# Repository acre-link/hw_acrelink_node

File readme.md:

# AcreLink Node

- Designed for a sleep current around 6 to 7 uA. 
- ESP32
- RFM95 Lora Module
- 868MHz PCB antenna, can be cut off and replaced by an SMA connector
- AA size lithium battery driven: (LS14500 Lithium-Thionyl-Chlorid or LifePo4 possible)
- Boost converter to supply sensors with stable 5V. Can be switched off for low current sleep mode
- External connector for Onewire, analog inputs and I2C including ESD protection with very low current TVS diodes
- Sensing battery voltage. Can be disabled for low sleep current
- Red led for signaling activity
- SPI header for external connection. 
- Mechanical switch to select battery of external power supply 
- Separate removable pcb section with wide range power supply 5 - 25V,  USB-C connector and USB-UART adapter for programming
- Enableable current measurement at GND level with 1 Ohm Resistor and low pass filtering. 
- Switchable Onewire power, data and datapullup, I2C power and pull ups. 

## 3D Preview 

## Pin Mapping ESP32
- AnalogInput1 : PIN13  GPIO14  ADC2_CH6
- Analog Bat   : PIN16  GPIO13  ADC2_CH4 
- AnalogInput2 : PIN11 GPIO26   ADC2_CH9
- I2C SDA	   : PIN33 GPIO21 		
- I2C SCL 	   : PIN36  GPIO22     
- UART2_RX     : PIN27 GPIO16        
- UART2_TX     : PIN28 GPIO17 		 
- 5V Buck EN   : PIN12 GPIO27 		
- LED_Signal   : PIN9 GPIO33
- RFM_MISO     : PIN31  GPIO19 
- RFM_MOSI     : PIN37  GPIO23 
- RFM_SCK      : PIN30  GPIO18
- RFM_CS       : PIN29  GPIO5
- RFM_RST      : PIN23  GPIO15 
- RFM_IRQ/DIO0 : PIN26  GPIO4 
- RFM_DIO1     : PIN8   GPIO32 	

## Links
- Antenna Design: https://github.com/cernohorsky/LoRa-Node  
- Selected soil sensor: https://de.aliexpress.com/item/1005001411485735.html?gatewayAdapt=glo2deu&spm=a2g0o.9042311.0.0.27424c4dQoBMf8 Supplyvoltage 3.6V - 30V.    Two analog outputs  0 to 2 V  for  soil temperature and soil humidity. ~5mA current consumption at 4V 

### Oher Links for reference
- https://www.metergroup.com/de/environment/produkte/teros-21/

- https://www.metergroup.com/de/environment/produkte/teros-10/

- https://www.metergroup.com/de/environment/

- https://de.aliexpress.com/item/32750933038.html?spm=a2g0o.productlist.0.0.62fa2b2dD94RVC&algo_pvid=56dd73b6-6484-4bd3-be9a-3d29279feaf3&algo_expid=56dd73b6-6484-4bd3-be9a-3d29279feaf3-32&btsid=2100bddb16056484973607092e316c&ws_ab_test=searchweb0_0,searchweb201602_,searchweb201603_

- https://de.aliexpress.com/store/915786

- https://www.ugt-online.de/produkte/bodenkunde/bodenfeuchtetemperaturleitfaehigkeit/sm150t/

- https://www.delta-t.co.uk/product/sm150t/

- https://de.aliexpress.com/item/32793236869.html?spm=a2g0s.8937460.0.0.3a672e0eRfM3vv

- Usefull for pin mapping: https://www.electroniclinic.com/esp32-wroom-32d-pinout-features-and-specifications/ 

- https://github.com/matthijskooijman/arduino-lmic#dio-pins  Lora requires at least DIO0 and DIO1

- https://jackgruber.github.io/2020-04-13-ESP32-DeepSleep-and-LoraWAN-OTAA-join/  Deep sleep lorawan

- SPI SD-Card header  //https://www.sparkfun.com/products/544 

- DC-DC Alternative: TP6841S6

## TODOs (next hw version)
- Cutout around USB-C ?
- Connectionpoint GNG-Current Measurement
- Alternative battery with more capacity: LS14500(2.6Ah), LS17500(3.6Ah) , LS26500(7.7Ah) ?    Solder directly to pcb without holder: LS [14,17,26]500CNA, TADIRAN SL360P  ?
- Change to Keystone 1015. Slightly longer but feel mechanically more robust.

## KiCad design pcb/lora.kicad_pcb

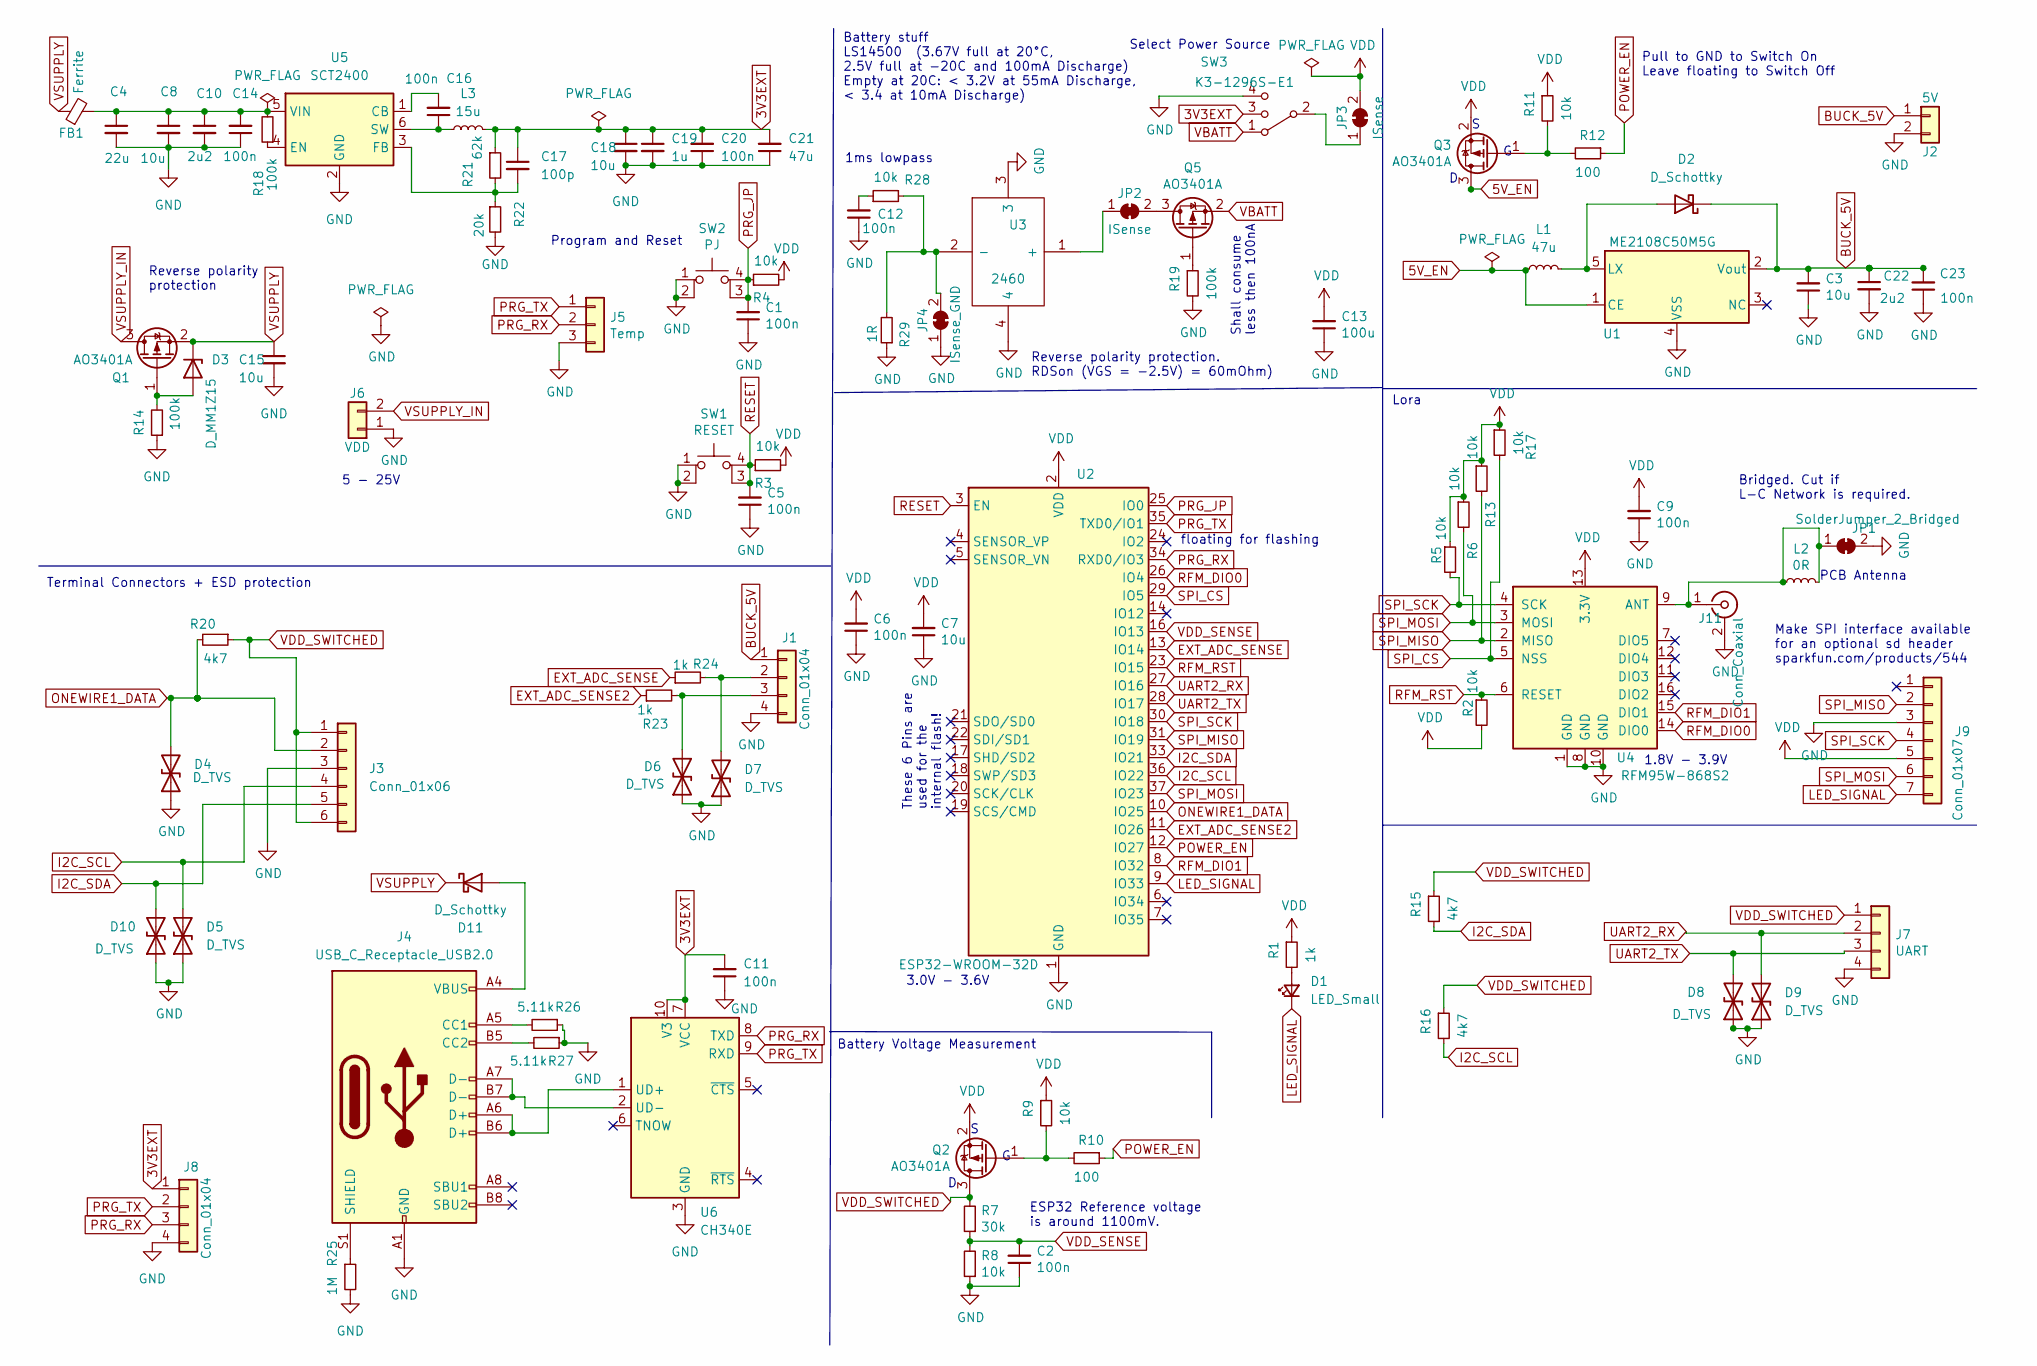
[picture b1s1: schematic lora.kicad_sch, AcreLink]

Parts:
C1, C2, C5, C6, C9, C11, C12, C14, C16, C20, C23: 100n; C_0603_1608Metric; LCSC C14663
C3, C8, C15, C18: 10u; C_0805_2012Metric; LCSC C440198
C4: 22u; C_1206_3216Metric; LCSC C342620
C7: 10u; C_0805_2012Metric; LCSC C15850
C10, C22: 2u2; C_0805_2012Metric; LCSC C49217
C13: 100u; C_1206_3216Metric; LCSC C15008
C17: 100p; C_0603_1608Metric; LCSC C14858
C19: 1u; C_0603_1608Metric; LCSC C90540
C21: 47u; C_1206_3216Metric; LCSC C96123
D1: LED_Small; LED_0603_1608Metric; LCSC C2286
D2, D11: D_Schottky; D_SOD-323; LCSC C122854
D3: D_MM1Z15; D_SOD-123; LCSC C86235
D4, D5, D6, D7, D8, D9, D10: D_TVS; D_0402_1005Metric; LCSC C2830311
FB1: Ferrite; L_0805_2012Metric; LCSC C1017
J1: Conn_01x04; TerminalBlock_TE_282834-4_1x04_P2.54mm_Horizontal
J2: 5V; pcb_edge_2_1
J3: Conn_01x06; TerminalBlock_TE_282834-6_1x06_P2.54mm_Horizontal
J4: USB_C_Receptacle_USB2.0; USB_C_Receptacle_HRO_TYPE-C-31-M-12; LCSC C167321
J5: Temp; PinHeader_1x03_P2.54mm_Vertical
J6: VDD; TerminalBlock_TE_282834-2_1x02_P2.54mm_Horizontal
J7: UART; pcb_edge_2_2
J8: Conn_01x04; PinHeader_1x04_P2.54mm_Vertical
J9: Conn_01x07; PinHeader_1x07_P2.54mm_Vertical
J11: Conn_Coaxial; SMA_Molex_73251-2120_EdgeMount_Horizontal
JP1: SolderJumper_2_Bridged; jumperhidden
JP2, JP3: ISense; SolderJumper-2_P1.3mm_Bridged_RoundedPad1.0x1.5mm
JP4: ISense_GND; SolderJumper-2_P1.3mm_Bridged_RoundedPad1.0x1.5mm
L1: 47u; L_SWPA4018S; LCSC C83445
L2: 0R; R_0603_1608Metric; LCSC C21189
L3: 15u; SLO0630H; LCSC C182182
Q1, Q2, Q3, Q5: AO3401A; SOT-23; LCSC C15127
R1, R23, R24: 1k; R_0603_1608Metric; LCSC C21190
R2, R3, R4, R5, R6, R8, R9, R11, R13, R17, R28: 10k; R_0603_1608Metric; LCSC C25804
R7: 30k; R_0603_1608Metric; LCSC C22984
R10, R12: 100; R_0603_1608Metric; LCSC C22775
R14, R18, R19: 100k; R_0603_1608Metric; LCSC C25803
R15, R16, R20: 4k7; R_0603_1608Metric; LCSC C23162
R21: 62k; R_0603_1608Metric; LCSC C23221
R22: 20k; R_0603_1608Metric; LCSC C4184
R25: 1M; R_0603_1608Metric; LCSC C22935
R26, R27: 5.11k; R_0603_1608Metric; LCSC C23067
R29: 1R; R_0603_1608Metric; LCSC C22936
SW1: RESET; TS-1187A-C-E-B; LCSC C318889
SW2: PJ; TS-1187A-C-E-B; LCSC C318889
SW3: K3-1296S-E1; LCSC C128955
U1: ME2108C50M5G; SOT-23-5_HandSoldering; LCSC C236790
U2: ESP32-WROOM-32D; ESP32-WROOM-32; LCSC C473012
U3: 2460; Mouser Part Number 534-2460
U4: RFM95W-868S2; HOPERF_RFM9XW_SMD
U5: SCT2400; TSOT-23-6; LCSC C2693819
U6: CH340E; MSOP-10_3x3mm_P0.5mm; LCSC C99652

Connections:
3V3EXT: C11.2, C17.1, C18.1, C19.1, C20.2, C21.2, J8.1, L3.2, R21.1, SW3.3, U6.7 (VCC), U6.10 (V3)
5V_EN: L1.1, Q3.3 (D), U1.1 (CE)
BUCK_5V: C3.2, C22.1, C23.2, D2.1 (K), J1.1, J2.1, U1.2 (Vout)
EXT_ADC_SENSE: R24.1, U2.13 (IO14)
EXT_ADC_SENSE2: R23.1, U2.11 (IO26)
GND: C1.1, C2.1, C3.1, C4.2, C5.1, C6.1, C7.1, C8.2, C9.1, C10.2, C11.1, C12.1, C13.1, C14.1, C15.2, C18.2, C19.2, C20.1, C21.1, C22.2, C23.1, D4.1 (A1), D5.1 (A1), D6.1 (A1), D7.1 (A1), D8.1 (A1), D9.1 (A1), D10.1 (A1), J1.4, J2.2, J3.3, J4.A1 (GND), J4.A12 (GND), J4.B1 (GND), J4.B12 (GND), J5.3, J6.1, J7.4, J8.4, J9.3, J11.2 (Ext), JP1.2 (B), JP4.1 (A), R8.1, R14.1, R19.2, R22.2, R25.2, R26.1, R27.1, R29.1, SW1.1, SW1.2, SW2.1, SW2.2, SW3.4, U1.4 (VSS), U2.1 (GND), U2.15 (GND), U2.38 (GND), U2.39 (GND), U3.3, U3.4, U4.1 (GND), U4.8 (GND), U4.10 (GND), U5.2 (GND), U6.3 (GND)
I2C_SCL: D5.2 (A2), J3.4, R16.2, U2.36 (IO22)
I2C_SDA: D10.2 (A2), J3.5, R15.2, U2.33 (IO21)
LED_SIGNAL: D1.1 (K), J9.7, U2.9 (IO33)
unnamed: C4.1, C8.1, C10.1, C14.2, FB1.2, R18.2, U5.5 (VIN)
unnamed: C12.2, R28.1
unnamed: C16.1, L3.1, U5.6 (SW)
unnamed: C16.2, U5.1 (CB)
unnamed: C17.2, R21.2, R22.1, U5.3 (FB)
unnamed: D1.2 (A), R1.2
unnamed: D2.2 (A), L1.2, U1.5 (LX)
unnamed: D3.2 (A), Q1.1 (G), R14.2
unnamed: D6.2 (A2), J1.3, R23.2
unnamed: D7.2 (A2), J1.2, R24.2
unnamed: D11.2 (A), J4.A4 (VBUS), J4.A9 (VBUS), J4.B4 (VBUS), J4.B9 (VBUS)
unnamed: J4.A5 (CC1), R26.2
unnamed: J4.A6 (D+), J4.B6 (D+), U6.1 (UD+)
unnamed: J4.A7 (D-), J4.B7 (D-), U6.2 (UD-)
unnamed: J4.B5 (CC2), R27.2
unnamed: J4.S1 (SHIELD), R25.1
unnamed: J11.1 (In), JP1.1 (A), L2.1, L2.2, U4.9 (ANT)
unnamed: JP2.1 (A), U3.1 (+)
unnamed: JP2.2 (B), Q5.3 (D)
unnamed: JP3.1 (A), SW3.2
unnamed: Q2.1 (G), R9.2, R10.2
unnamed: Q3.1 (G), R11.2, R12.2
unnamed: Q5.1 (G), R19.1
unnamed: R18.1, U5.4 (EN)
unnamed: JP4.2 (B), R28.2, R29.2, U3.2 (-)
ONEWIRE1_DATA: D4.2 (A2), J3.2, R20.2, U2.10 (IO25)
POWER_EN: R10.1, R12.1, U2.12 (IO27)
PRG_JP: C1.2, R4.1, SW2.3 (K), SW2.4 (A), U2.25 (IO0)
PRG_RX: J5.2, J8.3, U2.34 (RXD0/IO3), U6.8 (TXD)
PRG_TX: J5.1, J8.2, U2.35 (TXD0/IO1), U6.9 (RXD)
RESET: C5.2, R3.1, SW1.3 (K), SW1.4 (A), U2.3 (EN)
RFM_DIO0: U2.26 (IO4), U4.14 (DIO0)
RFM_DIO1: U2.8 (IO32), U4.15 (DIO1)
RFM_RST: R2.1, U2.23 (IO15), U4.6 (RESET)
SPI_CS: R17.2, U2.29 (IO5), U4.5 (NSS)
SPI_MISO: J9.2, R13.2, U2.31 (IO19), U4.2 (MISO)
SPI_MOSI: J9.6, R6.2, U2.37 (IO23), U4.3 (MOSI)
SPI_SCK: J9.4, R5.2, U2.30 (IO18), U4.4 (SCK)
UART2_RX: D9.2 (A2), J7.2, U2.27 (IO16)
UART2_TX: D8.2 (A2), J7.3, U2.28 (IO17)
VBATT: Q5.2 (S), SW3.1
VDD: C6.2, C7.2, C9.2, C13.2, J9.5, JP3.2 (B), Q2.2 (S), Q3.2 (S), R1.1, R2.2, R3.2, R4.2, R5.1, R6.1, R9.1, R11.1, R13.1, R17.1, U2.2 (VDD), U4.13 (3.3V)
VDD_SENSE: C2.2, R7.1, R8.2, U2.16 (IO13)
VDD_SWITCHED: J3.1, J3.6, J7.1, Q2.3 (D), R7.2, R15.1, R16.1, R20.1
VSUPPLY: C15.1, D3.1 (K), D11.1 (K), FB1.1, Q1.2 (S)
VSUPPLY_IN: J6.2, Q1.3 (D)

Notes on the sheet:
3.0V - 3.6V
5 - 25V
floating for flashing
1.8V - 3.9V
Battery stuff LS14500 (3.67V full at 20°C, 2.5V full at -20C and 100mA Discharge) Empty at 20C: < 3.2V at 55mA Discharge, < 3.4 at 10mA Discharge)
Terminal Connectors + ESD protection
These 6 Pins are used for the internal flash!
Program and Reset
PCB Antenna
Bridged. Cut if L-C Network is required.
Select Power Source
1ms lowpass
Battery Voltage Measurement
Pull to GND to Switch On Leave floating to Switch Off
Make SPI interface available for an optional sd header sparkfun.com/products/544
Lora
ESP32 Reference voltage is around 1100mV.
Shall consume less then 100nA
Reverse polarity protection. RDSon (VGS = -2.5V) = 60mOhm)
Reverse polarity protection

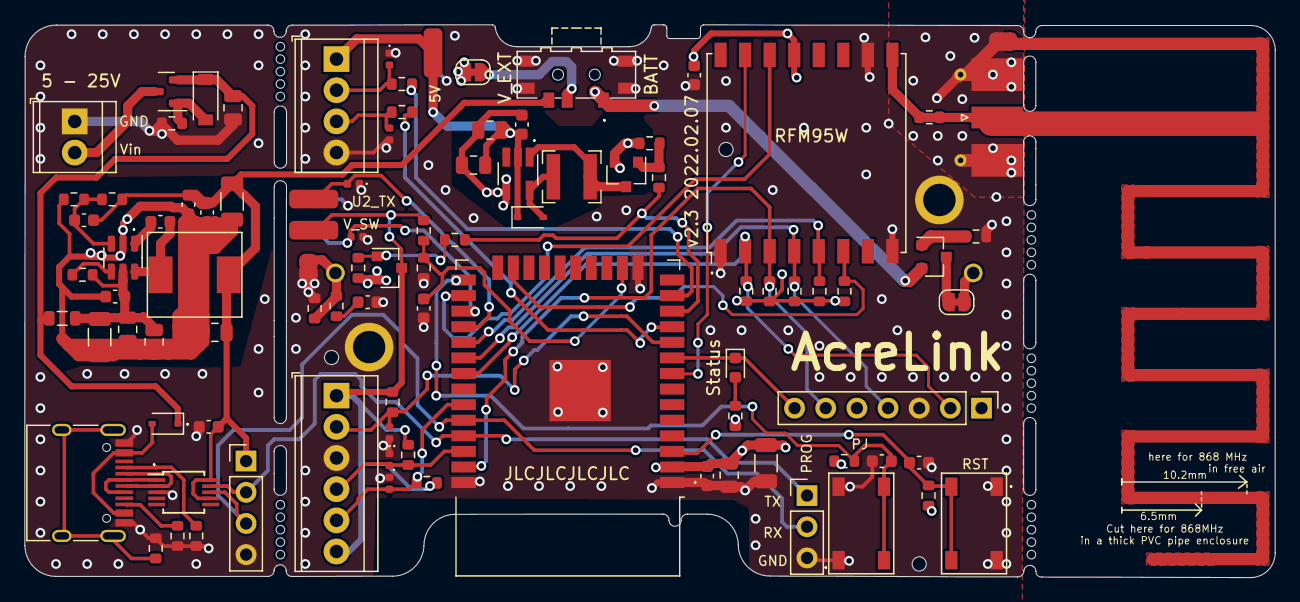
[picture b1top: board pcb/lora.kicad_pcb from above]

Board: 4 copper layers, 101.9 x 45.1 mm, 94 parts (1 on the bottom side), 55 nets.

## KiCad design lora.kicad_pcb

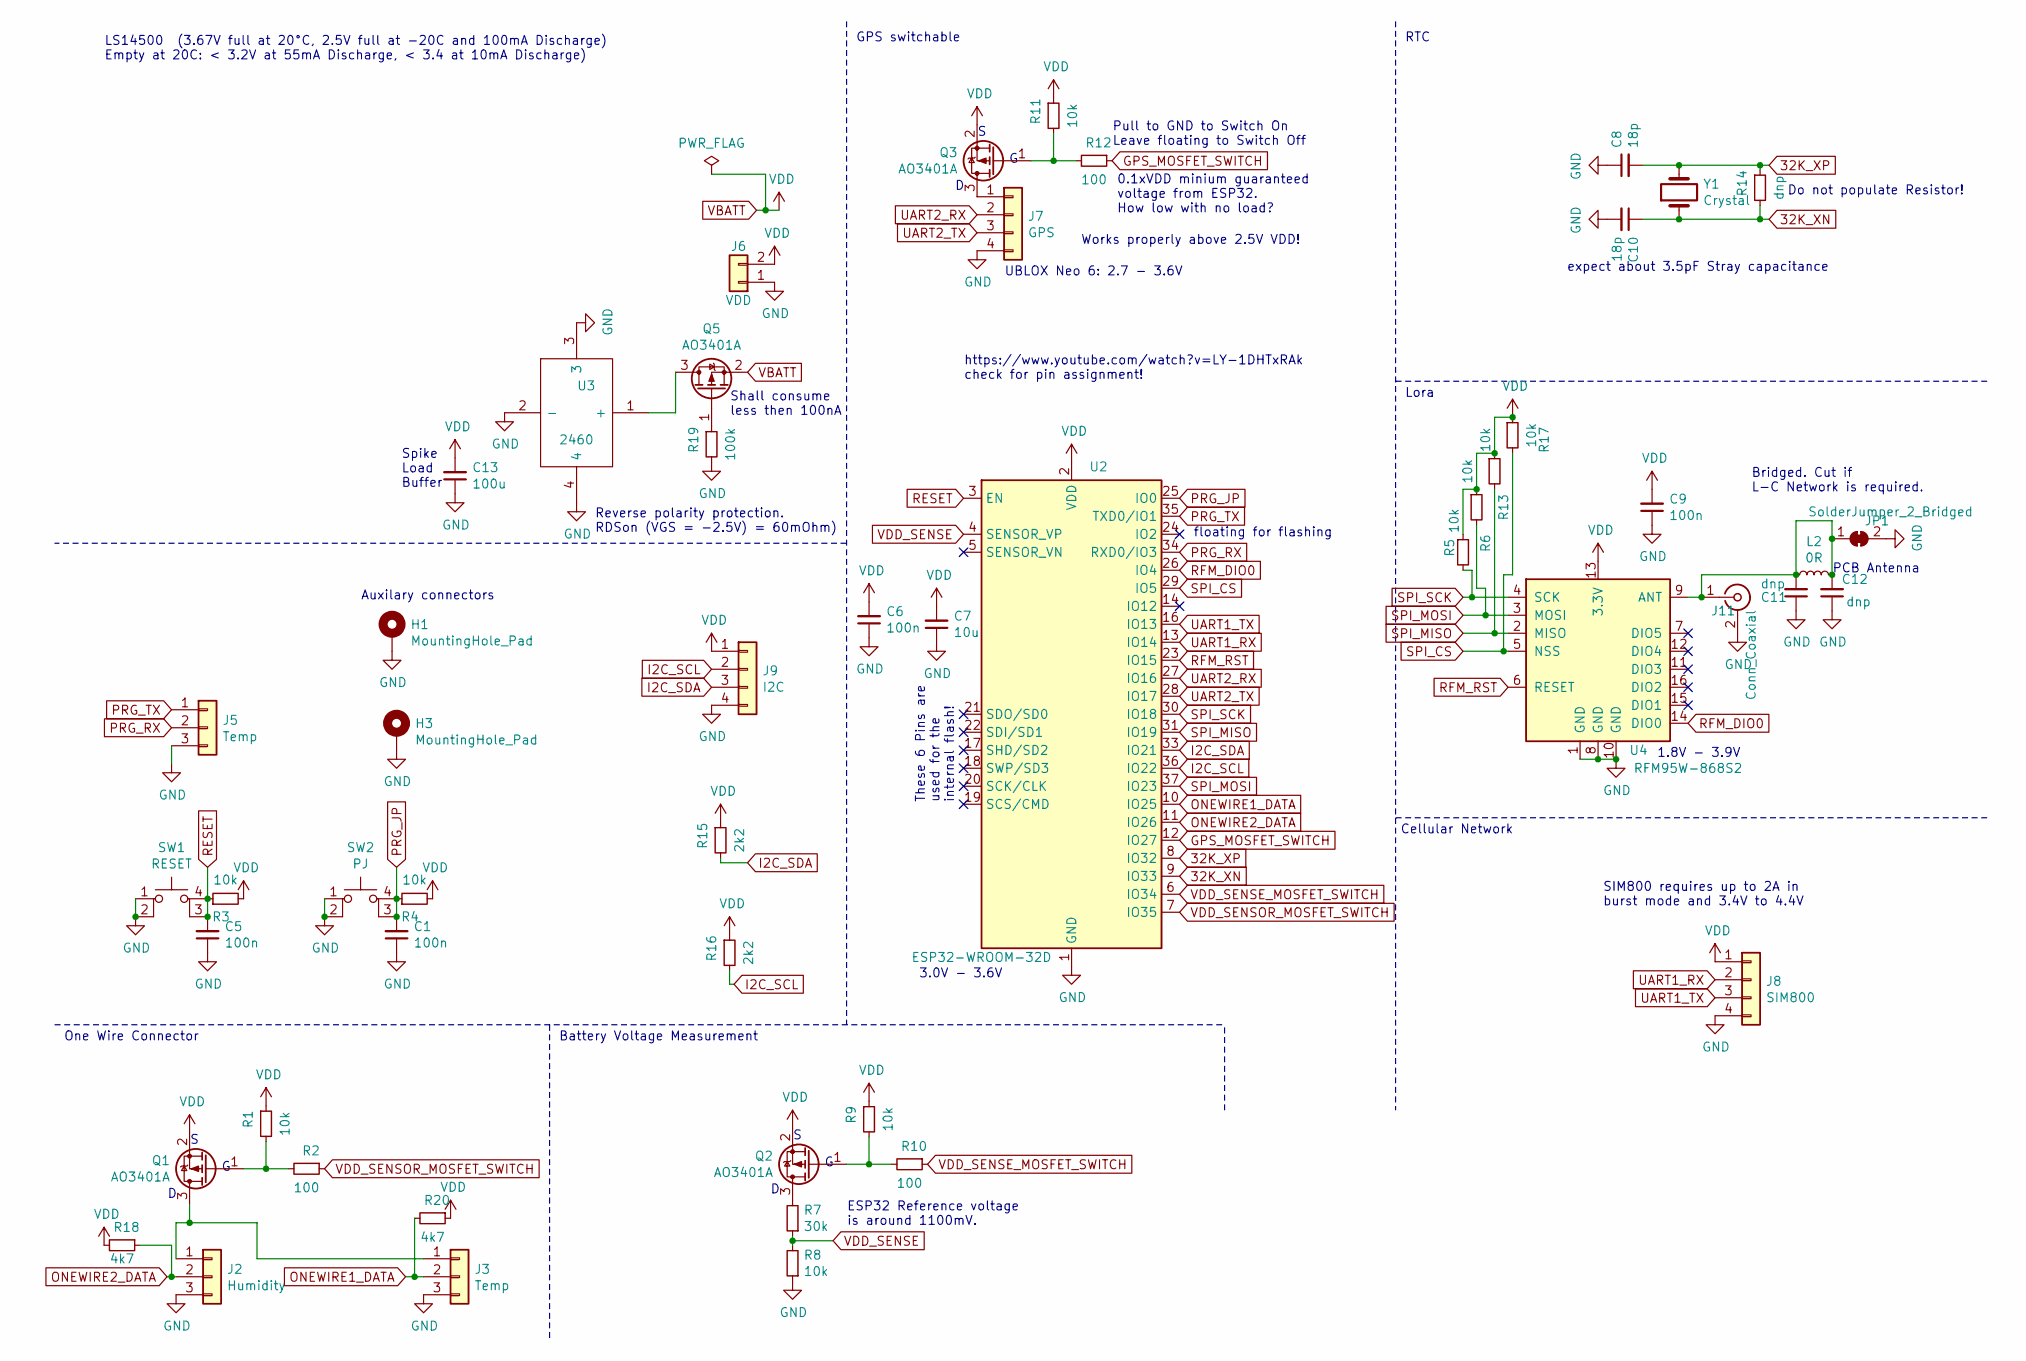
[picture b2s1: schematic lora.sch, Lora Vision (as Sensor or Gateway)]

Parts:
C1, C5, C6, C9: 100n; C_0603_1608Metric; LCSC C14663
C7: 10u; C_0805_2012Metric; LCSC C15850
C8, C10: 18p; C_0603_1608Metric; LCSC C1647
C11, C12: dnp; C_0603_1608Metric
C13: 100u; C_1206_3216Metric; LCSC C15008
H1, H3: MountingHole_Pad; MountingHole_2.2mm_M2_DIN965_Pad
J2: Humidity; PinHeader_1x03_P2.54mm_Horizontal
J3: Temp; PinHeader_1x03_P2.54mm_Horizontal
J5: Temp; PinHeader_1x03_P2.54mm_Vertical
J6: VDD; PinHeader_1x02_P2.54mm_Vertical
J7: GPS; PinHeader_1x04_P2.54mm_Vertical
J8: SIM800; PinHeader_1x04_P2.54mm_Vertical
J9: I2C; PinHeader_1x04_P2.54mm_Vertical
J11: Conn_Coaxial; SMA_Molex_73251-2120_EdgeMount_Horizontal
JP1: SolderJumper_2_Bridged; SolderJumper-2_P1.3mm_Bridged_Pad1.0x1.5mm
L2: 0R; R_0603_1608Metric; LCSC C21189
Q1, Q2, Q3, Q5: AO3401A; SOT-23; LCSC C15127
R1, R3, R4, R5, R6, R9, R11, R13, R17: 10k; C_0603_1608Metric; LCSC C25804
R2, R10, R12: 100; R_0603_1608Metric; LCSC C22775
R7: 30k; R_0603_1608Metric; LCSC C22984
R8: 10k; R_0603_1608Metric; LCSC C25804
R14: dnp; R_0603_1608Metric
R15, R16: 2k2; R_0603_1608Metric; LCSC C4190
R18, R20: 4k7; C_0603_1608Metric; LCSC C23162
R19: 100k; R_0603_1608Metric; LCSC C25803
SW1: RESET; TS-1187A-C-E-B; LCSC C318889
SW2: PJ; TS-1187A-C-E-B; LCSC C318889
U2: ESP32-WROOM-32D; ESP32-WROOM-32
U3: 2460; Mouser Part Number 534-2460
U4: RFM95W-868S2; HOPERF_RFM9XW_SMD
Y1: Crystal; Crystal_SMD_MicroCrystal_CC7V-T1A-2Pin_3.2x1.5mm; LCSC C32346

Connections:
32K_XN: C10.1, R14.2, U2.9 (IO33), Y1.1
32K_XP: C8.2, R14.1, U2.8 (IO32), Y1.2
GND: C1.1, C5.1, C6.1, C7.1, C8.1, C9.1, C10.2, C11.1, C12.1, C13.1, H1.1, H3.1, J2.3, J3.3, J5.3, J6.1, J7.4, J8.4, J9.4, J11.2 (Ext), JP1.2 (B), R8.1, R19.2, SW1.1, SW1.2, SW2.1, SW2.2, U2.1 (GND), U2.15 (GND), U2.38 (GND), U2.39 (GND), U3.2 (-), U3.3, U3.4, U4.1 (GND), U4.8 (GND), U4.10 (GND)
GPS_MOSFET_SWITCH: R12.1, U2.12 (IO27)
I2C_SCL: J9.2, R16.2, U2.36 (IO22)
I2C_SDA: J9.3, R15.2, U2.33 (IO21)
unnamed: C11.2, C12.2, J11.1 (In), JP1.1 (A), L2.1, L2.2, U4.9 (ANT)
unnamed: J2.1, J3.1, Q1.3 (D)
unnamed: J7.1, Q3.3 (D)
unnamed 9: U2.14 (IO12); also elsewhere on the board
unnamed: Q1.1 (G), R1.2, R2.2
unnamed: Q2.1 (G), R9.2, R10.2
unnamed: Q2.3 (D), R7.2
unnamed: Q3.1 (G), R11.2, R12.2
unnamed: Q5.1 (G), R19.1
unnamed: Q5.3 (D), U3.1 (+)
ONEWIRE1_DATA: J3.2, R20.2, U2.10 (IO25)
ONEWIRE2_DATA: J2.2, R18.1, U2.11 (IO26)
PRG_JP: C1.2, R4.1, SW2.3 (K), SW2.4 (A), U2.25 (IO0)
PRG_RX: J5.2, U2.34 (RXD0/IO3)
PRG_TX: J5.1, U2.35 (TXD0/IO1)
RESET: C5.2, R3.1, SW1.3 (K), SW1.4 (A), U2.3 (EN)
RFM_DIO0: U2.26 (IO4), U4.14 (DIO0)
RFM_RST: U2.23 (IO15), U4.6 (RESET)
SPI_CS: R17.2, U2.29 (IO5), U4.5 (NSS)
SPI_MISO: R13.2, U2.31 (IO19), U4.2 (MISO)
SPI_MOSI: R6.2, U2.37 (IO23), U4.3 (MOSI)
SPI_SCK: R5.2, U2.30 (IO18), U4.4 (SCK)
UART1_RX: J8.2, U2.13 (IO14)
UART1_TX: J8.3, U2.16 (IO13)
UART2_RX: J7.2, U2.27 (IO16)
UART2_TX: J7.3, U2.28 (IO17)
VBATT: C6.2, C7.2, C9.2, C13.2, J6.2, J8.1, J9.1, Q1.2 (S), Q2.2 (S), Q3.2 (S), Q5.2 (S), R1.1, R3.2, R4.2, R5.1, R6.1, R9.1, R11.1, R13.1, R15.1, R16.1, R17.1, R18.2, R20.1, U2.2 (VDD), U4.13 (3.3V); also elsewhere on the board
VDD_SENSE: R7.1, R8.2, U2.4 (SENSOR_VP)
VDD_SENSE_MOSFET_SWITCH: R10.1, U2.6 (IO34)
VDD_SENSOR_MOSFET_SWITCH: R2.1, U2.7 (IO35)

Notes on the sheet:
3.0V - 3.6V
Battery Voltage Measurement
RTC
One Wire Connector
Pull to GND to Switch On Leave floating to Switch Off
Works properly above 2.5V VDD!
0.1xVDD minium guaranteed voltage from ESP32. How low with no load?
ESP32 Reference voltage is around 1100mV.
1.8V - 3.9V
SIM800 requires up to 2A in burst mode and 3.4V to 4.4V
UBLOX Neo 6: 2.7 - 3.6V
Lora
Cellular Network
GPS switchable
Do not populate Resistor!
expect about 3.5pF Stray capacitance
Reverse polarity protection. RDSon (VGS = -2.5V) = 60mOhm)
Shall consume less then 100nA
Auxilary connectors
PCB Antenna
Bridged. Cut if L-C Network is required.
https://www.youtube.com/watch?v=LY-1DHTxRAk check for pin assignment!
These 6 Pins are used for the internal flash!
floating for flashing
Spike Load Buffer
LS14500 (3.67V full at 20°C, 2.5V full at -20C and 100mA Discharge) Empty at 20C: < 3.2V at 55mA Discharge, < 3.4 at 10mA Discharge)

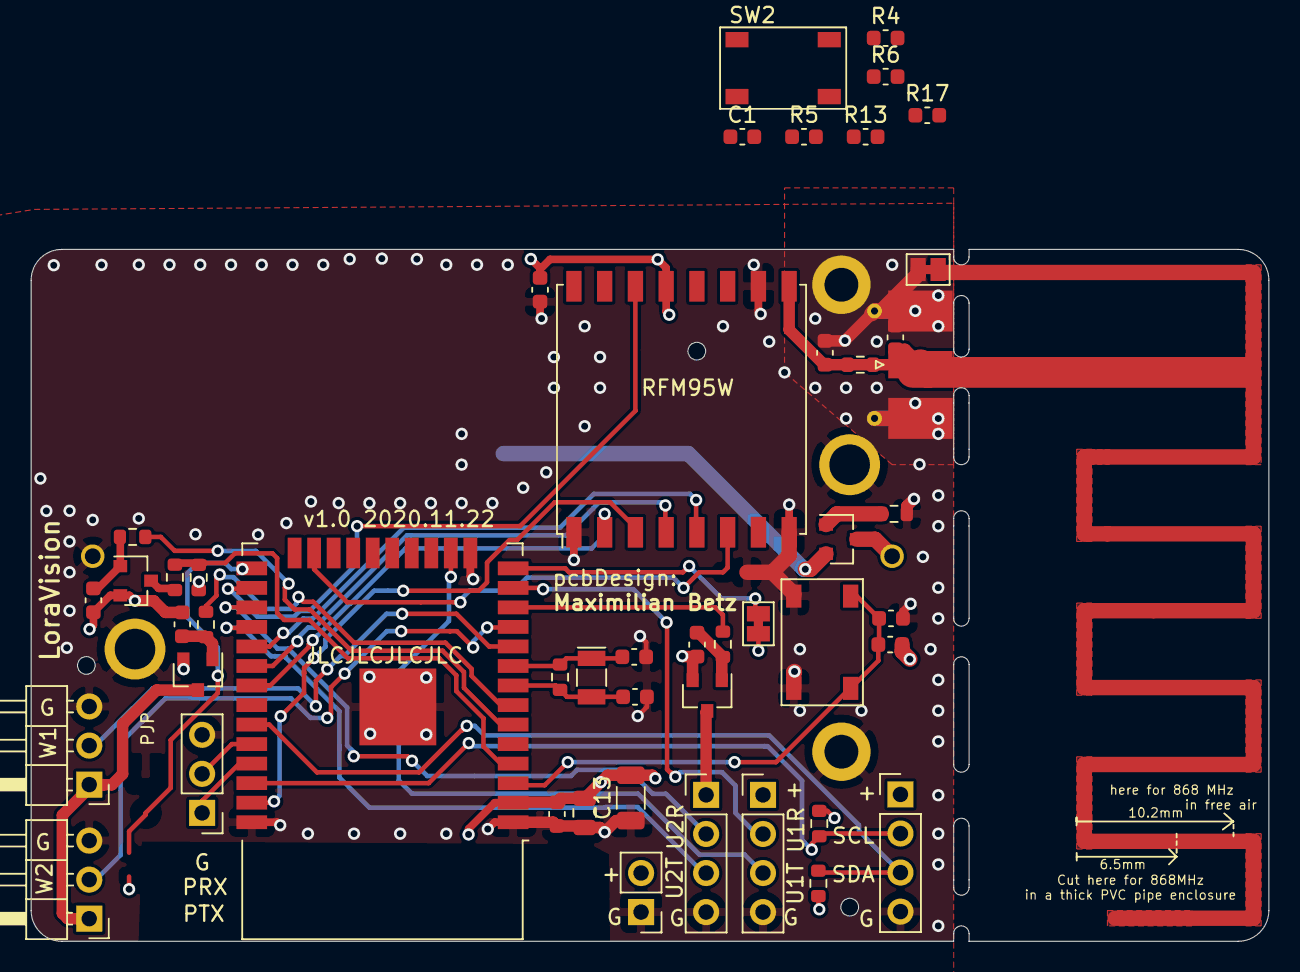
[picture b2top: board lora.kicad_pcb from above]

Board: 4 copper layers, 80.5 x 45.0 mm, 51 parts (1 on the bottom side), 36 nets.

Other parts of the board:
JP2: Bridged; SolderJumper-2_P1.3mm_Bridged_Pad1.0x1.5mm

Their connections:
unnamed 9: JP2.1; also elsewhere on the board
VBATT: JP2.2; also elsewhere on the board

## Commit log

2020-11-11 Initial import hw design
2020-11-15 minor updates
2020-11-15 finished dc dc power supply.
2020-11-15 nothing major
2020-11-16 removed RTC, added 32KHZ crystal to esp32.
2020-11-16 added reverse polarity protection.
2020-11-19 added reverse polarity protection for battery.
2020-11-19 created first net list. Created initial board and structured the componentes.
2020-11-19 some more structure and 2 additonal layers, first board outlines....
2020-11-22 some progress with layout. Added ferrit bead to schematic.
2020-11-22 added cutouts for antenna.
2020-11-22 added mounting holes for GPS
2020-11-22 plotted first gerber files.
2020-11-22 minor things
2020-11-22 schönen Lattenzaun! added Toolingholes, and JLCPCB number location.
2020-12-08 - updated pin assignment to recommended pins. - added 100uF capacity to buffer spike loads in battery mode.
2020-12-08 updated pcb from schematic.
2020-12-08 added page legend.
2020-12-09 pads gnd plane connection not solid to improve solderability.
2020-12-10 intermediate commit before removing a mounting hole
2020-12-10 almost done.. more work than expected to change the connector position and size
2020-12-10 finalized design and exchanges 220u capacity with a one in stock.
2020-12-10 generated gerber files, BOM, and footprint position files. footprint position file needs manual rotation adjustments.
2020-12-10 corrected wrong rotation. !!This is the ordered version!!
2020-12-11 received the production files from jlcpcb for review.
2021-01-03 added some more comments for next revision of pcb.
2021-01-04 another hint for second revision
2021-01-10 added some more hints for low sleep current in next revision.
2021-01-10 one more thing for next revision.
2021-01-10 two more links for esd protection hints.
2021-01-27 a hint added
2021-02-01 added cut line for antenna cut in PVC tube enclosure.
2021-03-07 added hint
2021-08-11 discussion for next version done
2021-09-07 corrected GND on input terminal
2021-09-07 remove rfm reset pulldown, add spi pullups, switch for programming added, labels backside added
2021-09-07 add onewire pullup
2021-09-07 remove JP2, add hints for StepUP DCDC
2021-09-07 updated part number step up
2021-09-07 hint added
2021-10-07 added label for antenna length
2021-10-16 add hint
2021-10-20 some steps done towards version 2. Progress recorded in hints.txt
2021-10-26 hints..
2021-11-07 some more hints after experiments
2022-01-27 cleaned up folder structure
2022-01-27 updated readmet
2022-01-27 added v1 schematic to media folder
2022-01-27 figured all GPIOs out
2022-01-29 intermediate commit
2022-01-29 schematic finalized
2022-01-29 add gitignore
2022-01-29 updated layout
2022-01-29 updated some text
2022-01-29 added usb - serial and external power supply
2022-01-30 fixed DRC errors
2022-01-30 more silkscreen text
2022-01-30 deleted old kicad v5 files
2022-01-30 changed a capacity
2022-01-30 added cutout for cable tie to secure battery
2022-01-31 added spi header and connected dio1 of rfm95
2022-01-31 updated 3d pitures for v2.1
2022-01-31 added v2.1 pdf schematic
2022-02-06 v2.2 finalized, spi connector added and ground current measurement solder jumper added
2022-02-07 added mouse bites for breakaway tabs
2022-08-03 comments only
2022-08-13 added hw picture
